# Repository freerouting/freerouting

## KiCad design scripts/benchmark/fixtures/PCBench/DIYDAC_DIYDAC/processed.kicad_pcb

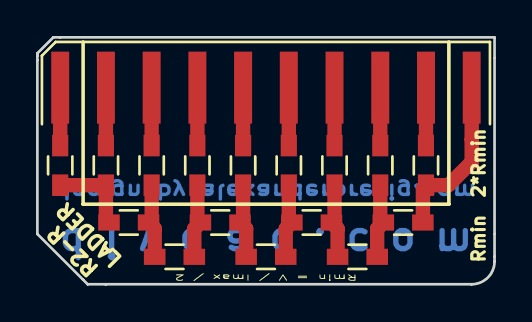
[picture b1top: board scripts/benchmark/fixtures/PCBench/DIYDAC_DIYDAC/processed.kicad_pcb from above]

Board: 2 copper layers, 25.4 x 13.7 mm, 17 parts (0 on the bottom side), 17 nets.

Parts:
2R0, 2R1, 2R2, 2R3, 2R4, 2R5, 2R6, 2R7, 2R8: R_0603_HandSoldering
P1: CONN_01X10; SMD_10P_100mil_laying_short
R1, R2, R3, R4, R5, R6, R7: R_0603_HandSoldering

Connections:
GND: 2R0.1, P1.1
unnamed: 2R0.2, 2R1.2, R1.1
unnamed: 2R1.1, P1.2
unnamed: 2R2.1, P1.3
unnamed: 2R2.2, R1.2, R2.1
unnamed: 2R3.1, P1.4
unnamed: 2R3.2, R2.2, R3.1
unnamed: 2R4.1, P1.5
unnamed: 2R4.2, R3.2, R4.1
unnamed: 2R5.1, P1.6
unnamed: 2R5.2, R4.2, R5.1
unnamed: 2R6.1, P1.7
unnamed: 2R6.2, R5.2, R6.1
unnamed: 2R7.1, P1.8
unnamed: 2R7.2, R6.2, R7.1
unnamed: 2R8.1, P1.9
unnamed: 2R8.2, P1.10, R7.2

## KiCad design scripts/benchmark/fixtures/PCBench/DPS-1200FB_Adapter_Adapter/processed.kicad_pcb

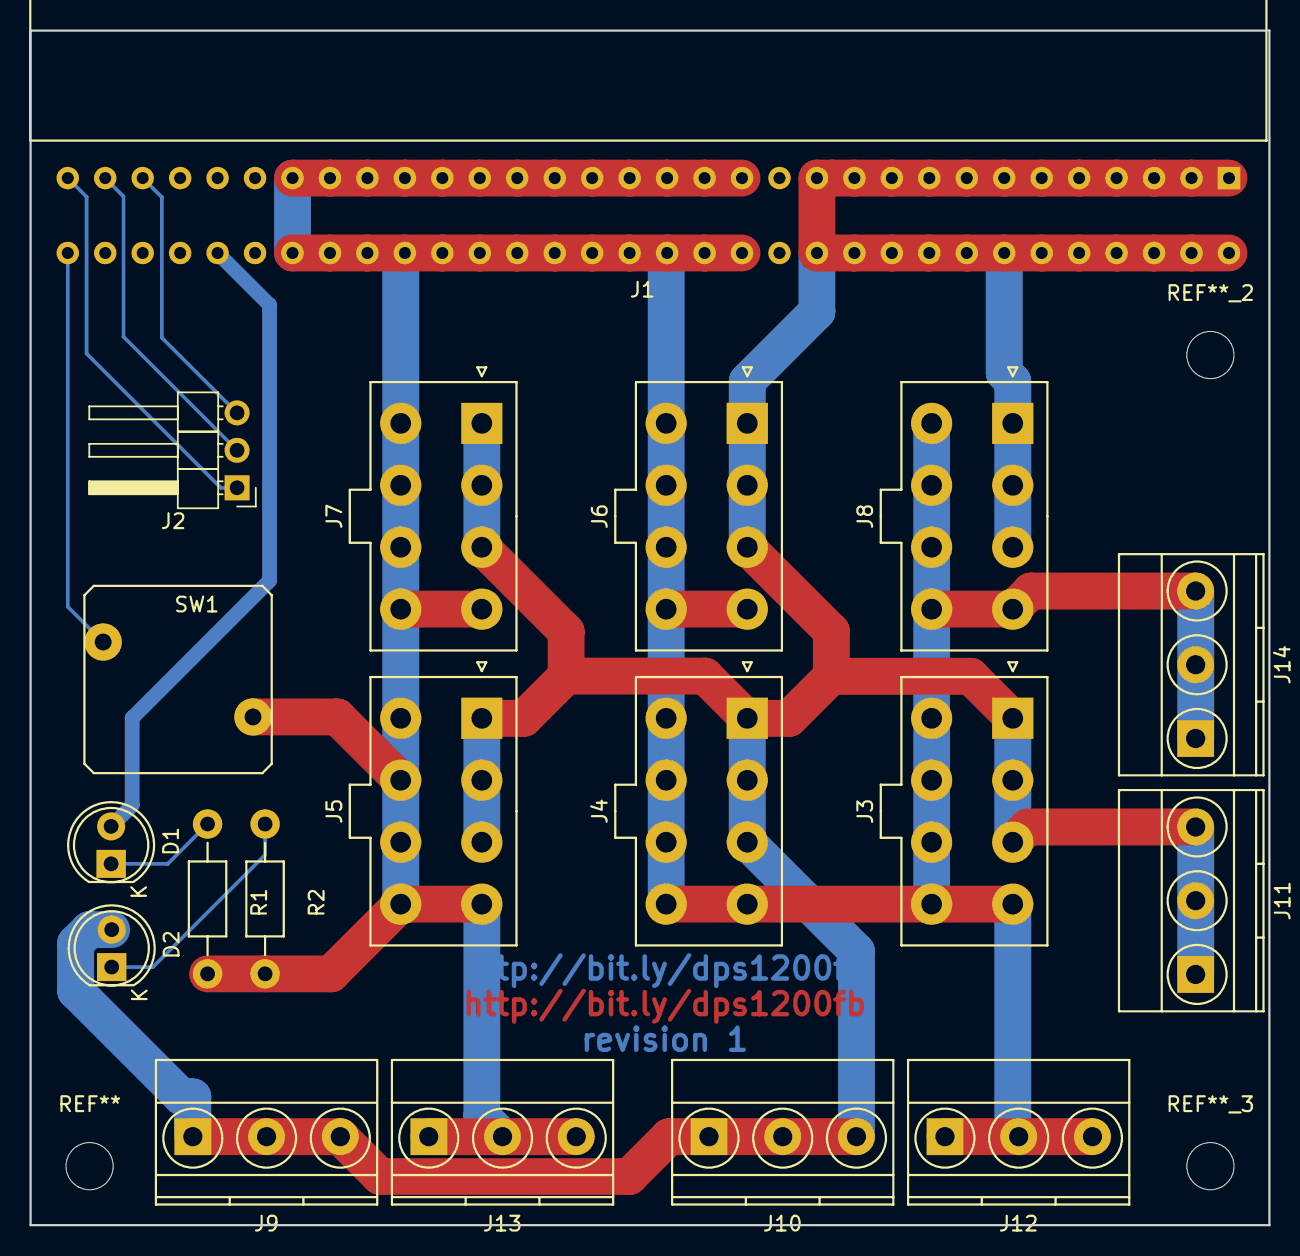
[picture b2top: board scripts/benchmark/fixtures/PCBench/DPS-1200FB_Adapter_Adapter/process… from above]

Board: 2 copper layers, 84.0 x 81.0 mm, 19 parts (0 on the bottom side), 9 nets.

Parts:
D1: LED_AMBER; LED-5MM
D2: LED_GREEN; LED-5MM
J1: PSU_CONNECTOR; COMMON_SLOT_PSU
J2: CONN_01X03; Pin_Header_Angled_1x03_Pitch2.54mm
J3, J4, J5, J6, J7, J8: PEG; Molex_MiniFit-JR-5556-08A_2x04x4.20mm_Straight
J9, J10, J11: 12V; TerminalBlock_Pheonix_MKDS1.5-3pol
J12, J13, J14: RTN; TerminalBlock_Pheonix_MKDS1.5-3pol
R1, R2: 560; Resistor_Horizontal_RM10mm
SW1: SW_SPST; SW_PUSH

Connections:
12V: D2.2, J1.1, J1.2, J1.3, J1.4, J1.5, J1.6, J1.7, J1.8, J1.9, J1.10, J1.11, J1.12, J1.53, J1.54, J1.55, J1.56, J1.57, J1.58, J1.59, J1.60, J1.61, J1.62, J1.63, J1.64, J3.1, J3.2, J3.3, J4.1, J4.2, J4.3, J5.1, J5.2, J5.3, J6.1, J6.2, J6.3, J7.1, J7.2, J7.3, J8.1, J8.2, J8.3, J9.1, J9.2, J9.3, J10.1, J10.2, J10.3, J11.1, J11.2, J11.3
12VSB: D1.2, J1.37
GND: J1.30, J2.3
unnamed: D1.1, R1.1
unnamed: D2.1, R2.1
PSON: J1.33, SW1.1
RTN: J1.14, J1.15, J1.16, J1.17, J1.18, J1.19, J1.20, J1.21, J1.22, J1.23, J1.24, J1.25, J1.26, J1.39, J1.40, J1.41, J1.42, J1.43, J1.44, J1.45, J1.46, J1.47, J1.48, J1.49, J1.50, J1.51, J3.4, J3.5, J3.6, J3.7, J3.8, J4.4, J4.5, J4.6, J4.7, J4.8, J5.4, J5.5, J5.6, J5.7, J5.8, J6.4, J6.5, J6.6, J6.7, J6.8, J7.4, J7.5, J7.6, J7.7, J7.8, J8.4, J8.5, J8.6, J8.7, J8.8, J12.1, J12.2, J12.3, J13.1, J13.2, J13.3, J14.1, J14.2, J14.3, R1.2, R2.2, SW1.2
SCL: J1.32, J2.1
SDA: J1.31, J2.2

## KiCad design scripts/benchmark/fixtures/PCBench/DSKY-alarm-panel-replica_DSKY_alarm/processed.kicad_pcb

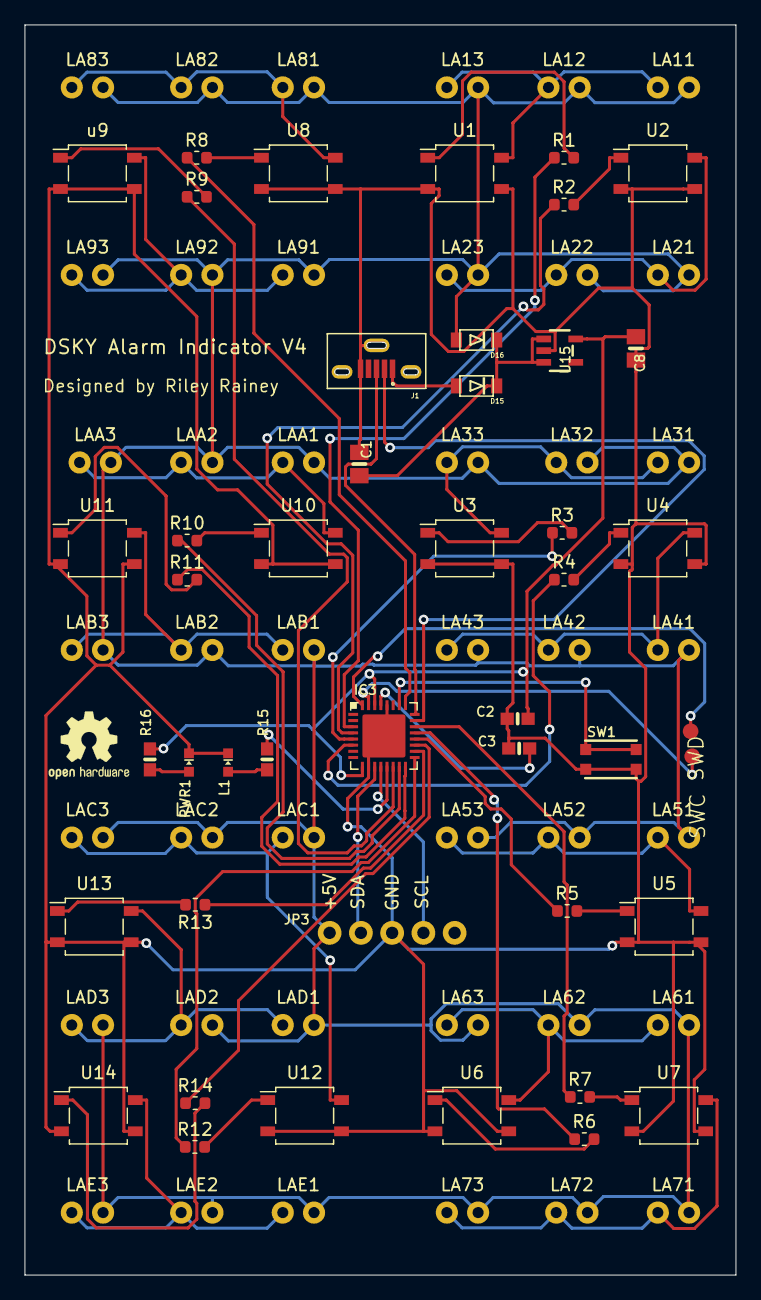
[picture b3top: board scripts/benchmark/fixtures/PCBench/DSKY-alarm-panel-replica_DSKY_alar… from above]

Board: 2 copper layers, 57.8 x 101.6 mm, 87 parts (0 on the bottom side), 58 nets.

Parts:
C1, C8: 10uF; 0805-NO
C2, C3: 1uF; 0603-NO
D15, D16: SCHOTTKY; SOD-123FL
IC3: ATSAMD21E; QFN32_5MM
J1: 105133-0001-MOLEX-USB; MOLEX_105133-0001
JP3: HEADER-1X576MIL; 1X05_ROUND_76
L1: red; CHIPLED_0603_NOOUTLINE
LA11, LA12, LA13, LA21, LA22, LA23, LA31, LA32, LA33, LA41, LA42, LA43, LA51, LA52, LA53, LA61, LA62, LA63, LA71, LA72, LA73, LA81, LA82, LA83, LA91, LA92, LA93: Lamp; VCC7216-ND
LAA1, LAA2, LAA3: Lamp; VCC7216-ND
LAB1, LAB2, LAB3: Lamp; VCC7216-ND
LAC1, LAC2, LAC3: Lamp; VCC7216-ND
LAD1, LAD2, LAD3: Lamp; VCC7216-ND
LAE1, LAE2, LAE3: Lamp; VCC7216-ND
PWR1: green; CHIPLED_0603_NOOUTLINE
R1, R2, R3, R4, R5, R6, R7, R8, R9, R10, R11, R12, R13, R14: 1.1K; R_0603_1608Metric
R15: 1.5K; 0603-NO
R16: 10K; 0603-NO
SW1: reset; BTN_KMR2_4.6X2.8
SWC: TPB1,27; B1,27
SWD: TPB1,27; B1,27
U1, U2, U3, U4, U5, U6, U7, U8, U10, U11, U12, U13, U14: AQY232SZ; SO-4_4.4x4.3mm_P2.54mm
U15: AP2112K-3.3; SOT23-5
u9: AQY232SZ; SO-4_4.4x4.3mm_P2.54mm

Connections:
3.3V: C2.1, C8.1, IC3.9, IC3.30, R16.2, U15.5
+5V: D16.A, JP3.1, LA11.2, LA12.2, LA13.2, LA21.2, LA22.2, LA23.2, LA31.2, LA32.2, LA33.2, LA41.2, LA42.2, LA43.2, LA51.2, LA52.2, LA53.2, LA61.2, LA62.2, LA63.2, LA71.2, LA72.2, LA73.2, LA81.2, LA82.2, LA83.2, LA91.2, LA92.2, LA93.2, LAA1.2, LAA2.2, LAA3.2, LAB1.2, LAB2.2, LAB3.2, LAC1.2, LAC2.2, LAC3.2, LAD1.2, LAD2.2, LAD3.2, LAE1.2, LAE2.2, LAE3.2
/D0_A4_PA08_SDA: IC3.11, JP3.2
/D2_A1_PA09_SCL_MISO: IC3.12, JP3.4
/D+: IC3.24, J1.3
/D-: IC3.23, J1.2
/VOUT: C1.1, D15.C, D16.C, U15.1, U15.3
/~RESET: IC3.26, SW1.A, SW1.A'
GND: C1.2, C2.2, C3.2, C8.2, IC3.10, IC3.28, IC3.33, J1.5, J1.S3, JP3.3, L1.C, PWR1.C, SW1.B, SW1.B', U1.2, U1.3, U2.2, U2.3, U3.2, U3.3, U4.2, U4.3, U5.2, U5.3, U6.2, U6.3, U7.2, U7.3, U8.2, U8.3, U10.2, U10.3, U11.2, U11.3, U12.2, U12.3, U13.2, U13.3, U14.2, U14.3, U15.2, u9.2, u9.3
LA1_PA02: IC3.3, R1.1
LA2_PA03: IC3.4, R2.1
LA3_PA04: IC3.5, R3.1
LA4_P05: IC3.6, R4.1
LA5_PA19: IC3.20, R5.1
LA6_PA22: IC3.21, R6.1
LA7_PA23: IC3.22, R7.1
LA8_PA27: IC3.25, R8.1
LA9_PA11: IC3.14, R9.1
LA10_PA14: IC3.15, R10.1
LA11_PA15: IC3.16, R11.1
LA12_PA16: IC3.17, R12.1
LA13_PA17: IC3.18, R13.1
LA14_PA18: IC3.19, R14.1
unnamed: C3.1, IC3.29
unnamed: IC3.13, R15.2
unnamed: IC3.31, SWC.TP
unnamed: IC3.32, SWD.TP
unnamed: L1.A, R15.1
unnamed: LA11.1, LA12.1, LA13.1, U1.4
unnamed: LA21.1, LA22.1, LA23.1, U2.4
unnamed: LA31.1, LA32.1, LA33.1, U3.4
unnamed: LA41.1, LA42.1, LA43.1, U4.4
unnamed: LA51.1, LA52.1, LA53.1, U5.4
unnamed: LA61.1, LA62.1, LA63.1, U6.4
unnamed: LA71.1, LA72.1, LA73.1, U7.4
unnamed: LA81.1, LA82.1, LA83.1, U8.4
unnamed: LA91.1, LA92.1, LA93.1, u9.4
unnamed: LAA1.1, LAA2.1, LAA3.1, U10.4
unnamed: LAB1.1, LAB2.1, LAB3.1, U11.4
unnamed: LAC1.1, LAC2.1, LAC3.1, U12.4
unnamed: LAD1.1, LAD2.1, LAD3.1, U13.4
unnamed: LAE1.1, LAE2.1, LAE3.1, U14.4
unnamed: PWR1.A, R16.1
unnamed: R1.2, U1.1
unnamed: R2.2, U2.1
unnamed: R3.2, U3.1
unnamed: R4.2, U4.1
unnamed: R5.2, U5.1
unnamed: R6.2, U6.1
unnamed: R7.2, U7.1
unnamed: R8.2, U8.1
unnamed: R9.2, u9.1
unnamed: R10.2, U10.1
unnamed: R11.2, U11.1
unnamed: R12.2, U12.1
unnamed: R13.2, U13.1
unnamed: R14.2, U14.1
VBUS: D15.A, J1.1
